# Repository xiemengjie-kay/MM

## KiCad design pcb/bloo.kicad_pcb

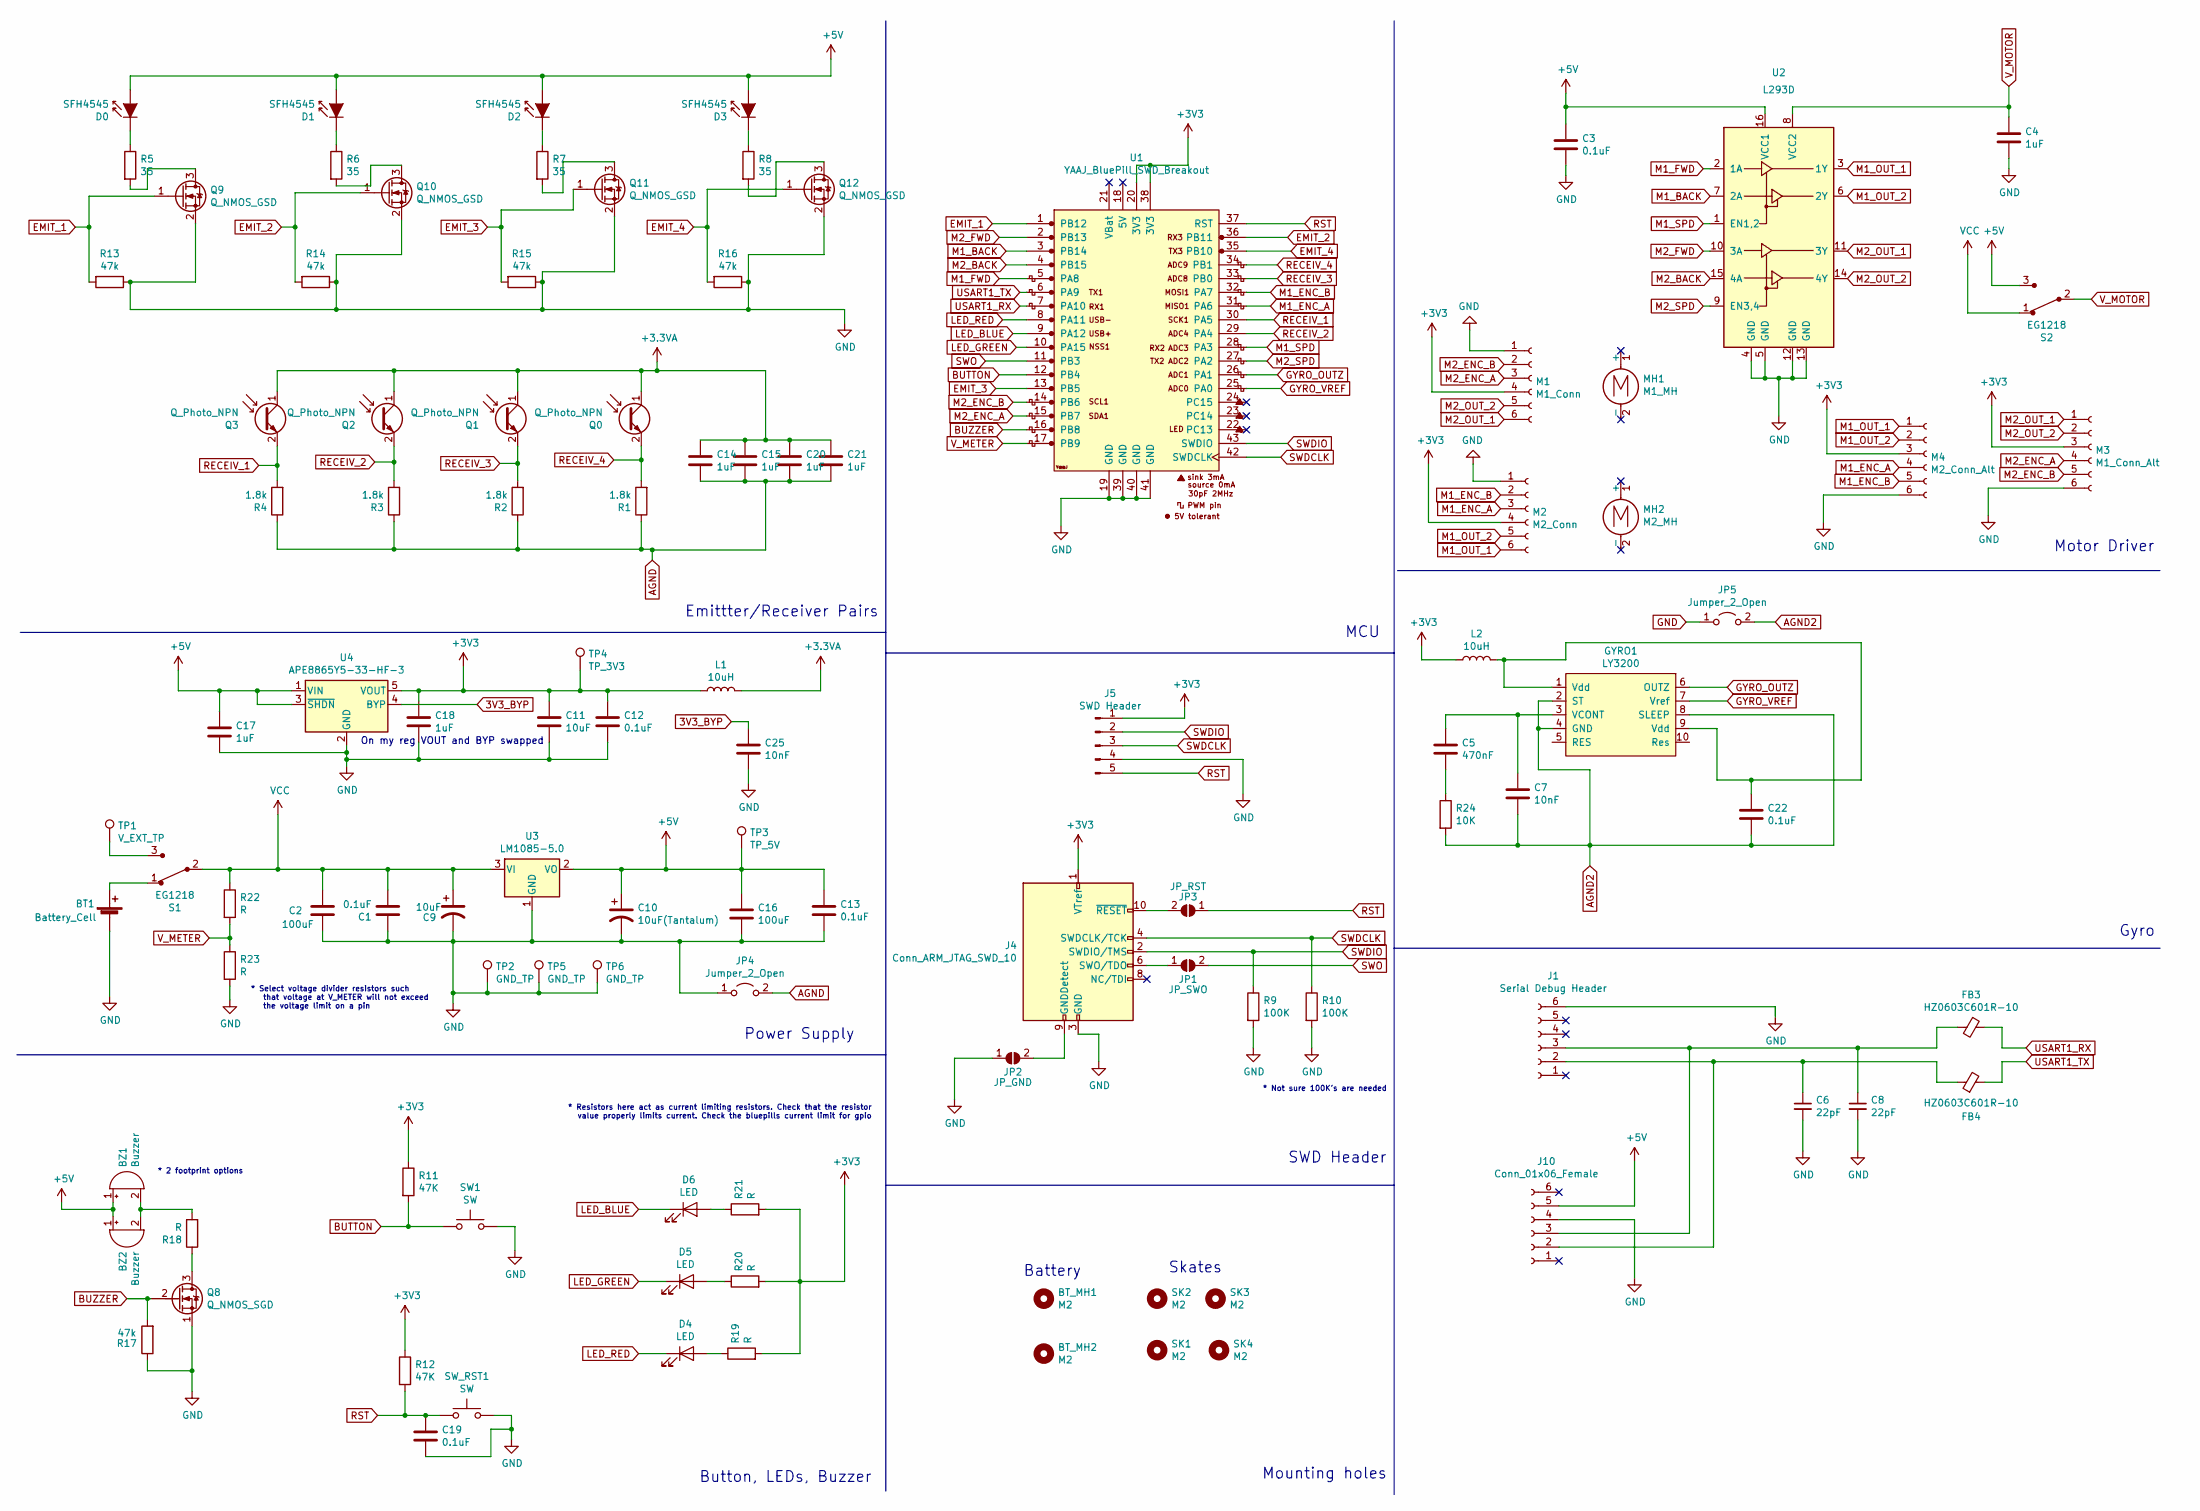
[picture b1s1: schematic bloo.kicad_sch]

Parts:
BT1: Battery_Cell; PinSocket_1x02_P2.54mm_Vertical
BT_MH1, BT_MH2: M2; MountingHole_2.2mm_M2
BZ1: Buzzer; Buzzer_12x9.5RM7.6
BZ2: Buzzer; Buzzer_TDK_PS1240P02BT_D12.2mm_H6.5mm
C1, C3, C12, C13, C19, C22: 0.1uF; C_1206_3216Metric_Pad1.33x1.80mm_HandSolder
C2, C16: 100uF; CP_Radial_D6.3mm_P2.50mm
C4, C14, C15, C17, C18, C20, C21: 1uF; C_1206_3216Metric_Pad1.33x1.80mm_HandSolder
C5: 470nF; C_1206_3216Metric_Pad1.33x1.80mm_HandSolder
C6, C8: 22pF; C_0603_1608Metric_Pad1.08x0.95mm_HandSolder
C7, C25: 10nF; C_1206_3216Metric_Pad1.33x1.80mm_HandSolder
C9, C11: 10uF; C_1206_3216Metric_Pad1.33x1.80mm_HandSolder
C10: 10uF(Tantalum); C_1206_3216Metric_Pad1.33x1.80mm_HandSolder
D0, D1, D2, D3: SFH4545; Emitter
D4, D5, D6: LED; LED_0805_2012Metric_Pad1.15x1.40mm_HandSolder
FB3, FB4: HZ0603C601R-10; R_0603_1608Metric_Pad0.98x0.95mm_HandSolder
GYRO1: LY3200; LGA10
J1: Serial Debug Header; PinHeader_1x06_P2.54mm_Vertical
J4: Conn_ARM_JTAG_SWD_10; PinHeader_2x05_P1.27mm_Vertical
J5: SWD Header; PinHeader_1x05_P2.54mm_Vertical
J10: Conn_01x06_Female; PinSocket_1x06_P2.54mm_Vertical
JP1: JP_SWO; SolderJumper-2_P1.3mm_Open_Pad1.0x1.5mm
JP2: JP_GND; SolderJumper-2_P1.3mm_Open_Pad1.0x1.5mm
JP3: JP_RST; SolderJumper-2_P1.3mm_Open_Pad1.0x1.5mm
JP4, JP5: Jumper_2_Open; SolderJumper-2_P1.3mm_Bridged_Pad1.0x1.5mm
L1, L2: 10uH; L_1206_3216Metric_Pad1.42x1.75mm_HandSolder
M1: M1_Conn; JST_SH_BM06B-SRSS-TB_1x06-1MP_P1.00mm_Vertical
M2: M2_Conn; JST_SH_BM06B-SRSS-TB_1x06-1MP_P1.00mm_Vertical
M3: M1_Conn_Alt; PinHeader_1x06_P2.54mm_Vertical
M4: M2_Conn_Alt; PinHeader_1x06_P2.54mm_Vertical
MH1: M1_MH; Motor_mouse
MH2: M2_MH; Motor_mouse
Q0, Q1, Q2, Q3: Q_Photo_NPN; Emitter
Q8: Q_NMOS_SGD; SOT-23
Q9, Q10, Q11, Q12: Q_NMOS_GSD; SOT-23
R1, R2, R3, R4: 1.8k; R_1206_3216Metric_Pad1.30x1.75mm_HandSolder
R5, R6, R7, R8: 35; R_1206_3216Metric_Pad1.30x1.75mm_HandSolder
R9, R10: 100K; R_1206_3216Metric_Pad1.30x1.75mm_HandSolder
R11, R12: 47K; R_1206_3216Metric_Pad1.30x1.75mm_HandSolder
R13, R14, R15, R16, R17: 47k; R_1206_3216Metric_Pad1.30x1.75mm_HandSolder
R18, R19, R20, R21, R22, R23: R; R_1206_3216Metric_Pad1.30x1.75mm_HandSolder
R24: 10K; R_1206_3216Metric_Pad1.30x1.75mm_HandSolder
S1, S2: EG1218; 1103M2S4CQE2; MPN EG1218; Digi-Key_PN EG1903-ND
SK1, SK2, SK3, SK4: M2; MountingHole_2.2mm_M2
SW1: SW; SW_SPST_REED_CT05-XXXX-G1
SW_RST1: SW; SW_SPST_REED_CT05-XXXX-G1
TP1: V_EXT_TP; PinHeader_1x01_P2.54mm_Vertical
TP2, TP5, TP6: GND_TP; PinHeader_1x01_P2.54mm_Vertical
TP3: TP_5V; PinHeader_1x01_P2.54mm_Vertical
TP4: TP_3V3; PinHeader_1x01_P2.54mm_Vertical
U1: YAAJ_BluePill_SWD_Breakout; YAAJ_BluePill_SWD_2
U2: L293D; DIP-16_W7.62mm
U3: LM1085-5.0; VREG_TO-263-3_TabPin2
U4: APE8865Y5-33-HF-3; SOT-23-5

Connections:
3V3_BYP: C25.1, U4.4 (BYP)
+3.3VA: C14.1, C15.1, C20.1, C21.1, L1.2, Q0.1 (C), Q1.1 (C), Q2.1 (C), Q3.1 (C)
+3V3: C11.1, C12.1, C18.1, J4.1 (VTref), J5.1, L1.1, L2.1, M1.4, M2.4, M3.3, M4.3, R11.1, R12.1, R19.2, R20.2, R21.2, TP4.1, U1.20 (3V3), U1.38 (3V3), U4.5 (VOUT); also elsewhere on the board
+5V: BZ1.1 (-), BZ2.1 (-), C3.1, C10.1, C13.1, C16.1, C17.1, D0.2 (A), D1.2 (A), D2.2 (A), D3.2 (A), J10.5, S2.3, TP3.1, U2.16 (VCC1), U3.2 (VO), U4.1 (VIN), U4.3 (~SHDN); also elsewhere on the board
AGND: C14.2, C15.2, C20.2, C21.2, JP4.2 (B), R1.1, R2.1, R3.1, R4.1
AGND2: C7.2, C22.2, GYRO1.2 (ST), GYRO1.4 (GND), GYRO1.8 (SLEEP), JP5.2 (B), R24.2
BUTTON: R11.2, SW1.1, U1.12 (PB4)
BUZZER: Q8.2 (G), R17.2, U1.16 (PB8)
EMIT_1: Q9.1 (G), R13.2, U1.1 (PB12)
EMIT_2: Q10.1 (G), R14.2, U1.36 (PB11)
EMIT_3: Q11.1 (G), R15.2, U1.13 (PB5)
EMIT_4: Q12.1 (G), R16.2, U1.35 (PB10)
GND: BT1.2 (-), C1.1, C2.2, C3.2, C4.2, C6.2, C8.2, C9.2, C10.2, C11.2, C12.2, C13.2, C16.2, C17.2, C18.2, C19.2, C25.2, J1.6, J4.3 (GND), J4.5 (GND), J5.4, J10.4, JP2.1 (A), JP4.1 (A), JP5.1 (A), M1.1, M2.1, M3.6, M4.6, Q8.1 (S), Q9.2 (S), Q10.2 (S), Q11.2 (S), Q12.2 (S), R9.2, R10.2, R13.1, R14.1, R15.1, R16.1, R17.1, R23.2, SW1.2, SW_RST1.2, TP2.1, TP5.1, TP6.1, U1.19 (GND), U1.39 (GND), U1.40 (GND), U1.41 (GND), U2.4 (GND), U2.5 (GND), U2.12 (GND), U2.13 (GND), U3.1 (GND), U4.2 (GND); also elsewhere on the board
GYRO_OUTZ: GYRO1.6 (OUTZ), U1.26 (PA1)
GYRO_VREF: GYRO1.7 (Vref), U1.25 (PA0)
LED_BLUE: D6.1 (K), U1.9 (PA12)
LED_GREEN: D5.1 (K), U1.10 (PA15)
LED_RED: D4.1 (K), U1.8 (PA11)
M1_BACK: U1.3 (PB14), U2.7 (2A)
M1_ENC_A: M2.3, M4.4, U1.31 (PA6)
M1_ENC_B: M2.2, M4.5, U1.32 (PA7)
M1_FWD: U1.5 (PA8), U2.2 (1A)
M1_OUT_1: M2.6, M4.1, U2.3 (1Y)
M1_OUT_2: M2.5, M4.2, U2.6 (2Y)
M1_SPD: U1.28 (PA3), U2.1 (EN1,2)
M2_BACK: U1.4 (PB15), U2.15 (4A)
M2_ENC_A: M1.3, M3.4, U1.15 (PB7)
M2_ENC_B: M1.2, M3.5, U1.14 (PB6)
M2_FWD: U1.2 (PB13), U2.10 (3A)
M2_OUT_1: M1.6, M3.1, U2.11 (3Y)
M2_OUT_2: M1.5, M3.2, U2.14 (4Y)
M2_SPD: U1.27 (PA2), U2.9 (EN3,4)
unnamed: BT1.1 (+), S1.1
unnamed: BZ1.2 (+), BZ2.2 (+), R18.2
unnamed: C5.1, C7.1, GYRO1.3 (VCONT)
unnamed: C5.2, R24.1
unnamed 36: C6.1, FB4.1, J1.2, J10.2; also elsewhere on the board
unnamed 37: C8.1, FB3.2, J1.3, J10.3; also elsewhere on the board
unnamed: C22.1, GYRO1.1 (Vdd), GYRO1.9 (Vdd), L2.2
unnamed: D0.1 (K), R5.1
unnamed: D1.1 (K), R6.1
unnamed: D2.1 (K), R7.1
unnamed: D3.1 (K), R8.1
unnamed: D4.2 (A), R19.1
unnamed: D5.2 (A), R20.1
unnamed: D6.2 (A), R21.1
unnamed: J4.6 (SWO/TDO), JP1.1 (A)
unnamed: J4.9 (GNDDetect), JP2.2 (B)
unnamed: J4.10 (~RESET), JP3.2 (B)
unnamed: Q8.3 (D), R18.1
unnamed: Q9.3 (D), R5.2
unnamed: Q10.3 (D), R6.2
unnamed: Q11.3 (D), R7.2
unnamed: Q12.3 (D), R8.2
unnamed: S1.3, TP1.1
RECEIV_1: Q3.2 (E), R4.2, U1.30 (PA5)
RECEIV_2: Q2.2 (E), R3.2, U1.29 (PA4)
RECEIV_3: Q1.2 (E), R2.2, U1.33 (PB0)
RECEIV_4: Q0.2 (E), R1.2, U1.34 (PB1)
RST: C19.1, J5.5, JP3.1 (A), R12.2, SW_RST1.1, U1.37 (RST); also elsewhere on the board
SWDCLK: J4.4 (SWDCLK/TCK), J5.3, R10.1, U1.42 (SWDCLK)
SWDIO: J4.2 (SWDIO/TMS), J5.2, R9.1, U1.43 (SWDIO)
SWO: JP1.2 (B), U1.11 (PB3)
USART1_RX: FB3.1, U1.7 (PA10)
USART1_TX: FB4.2, U1.6 (PA9)
VCC: C1.2, C2.1, C9.1, R22.1, S1.2, S2.1, U3.3 (VI)
V_METER: R22.2, R23.1, U1.17 (PB9)
V_MOTOR: C4.1, S2.2, U2.8 (VCC2)

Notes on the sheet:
SWD Header
* Resistors here act as current limiting resistors. Check that the resistor value properly limits current. Check the bluepills current limit for gpio
Emittter/Receiver Pairs
Motor Driver
Button, LEDs, Buzzer
MCU
Skates
Mounting holes
* Select voltage divider resistors such that voltage at V_METER will not exceed the voltage limit on a pin
Gyro
On my reg VOUT and BYP swapped
Battery
* 2 footprint options
Power Supply
* Not sure 100K’s are needed

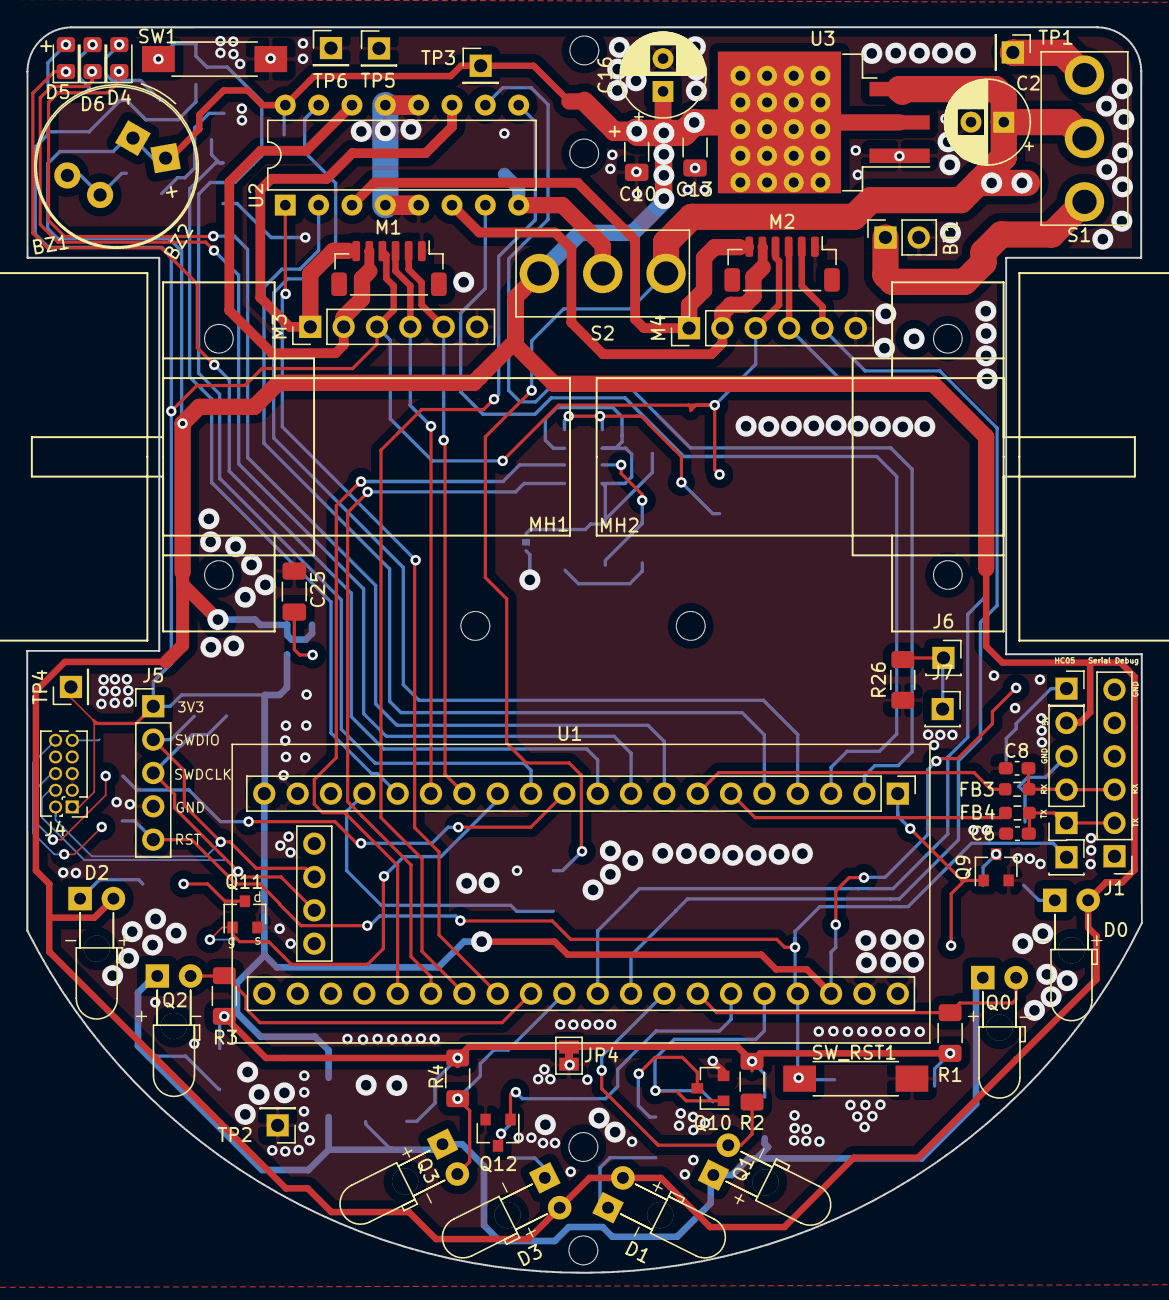
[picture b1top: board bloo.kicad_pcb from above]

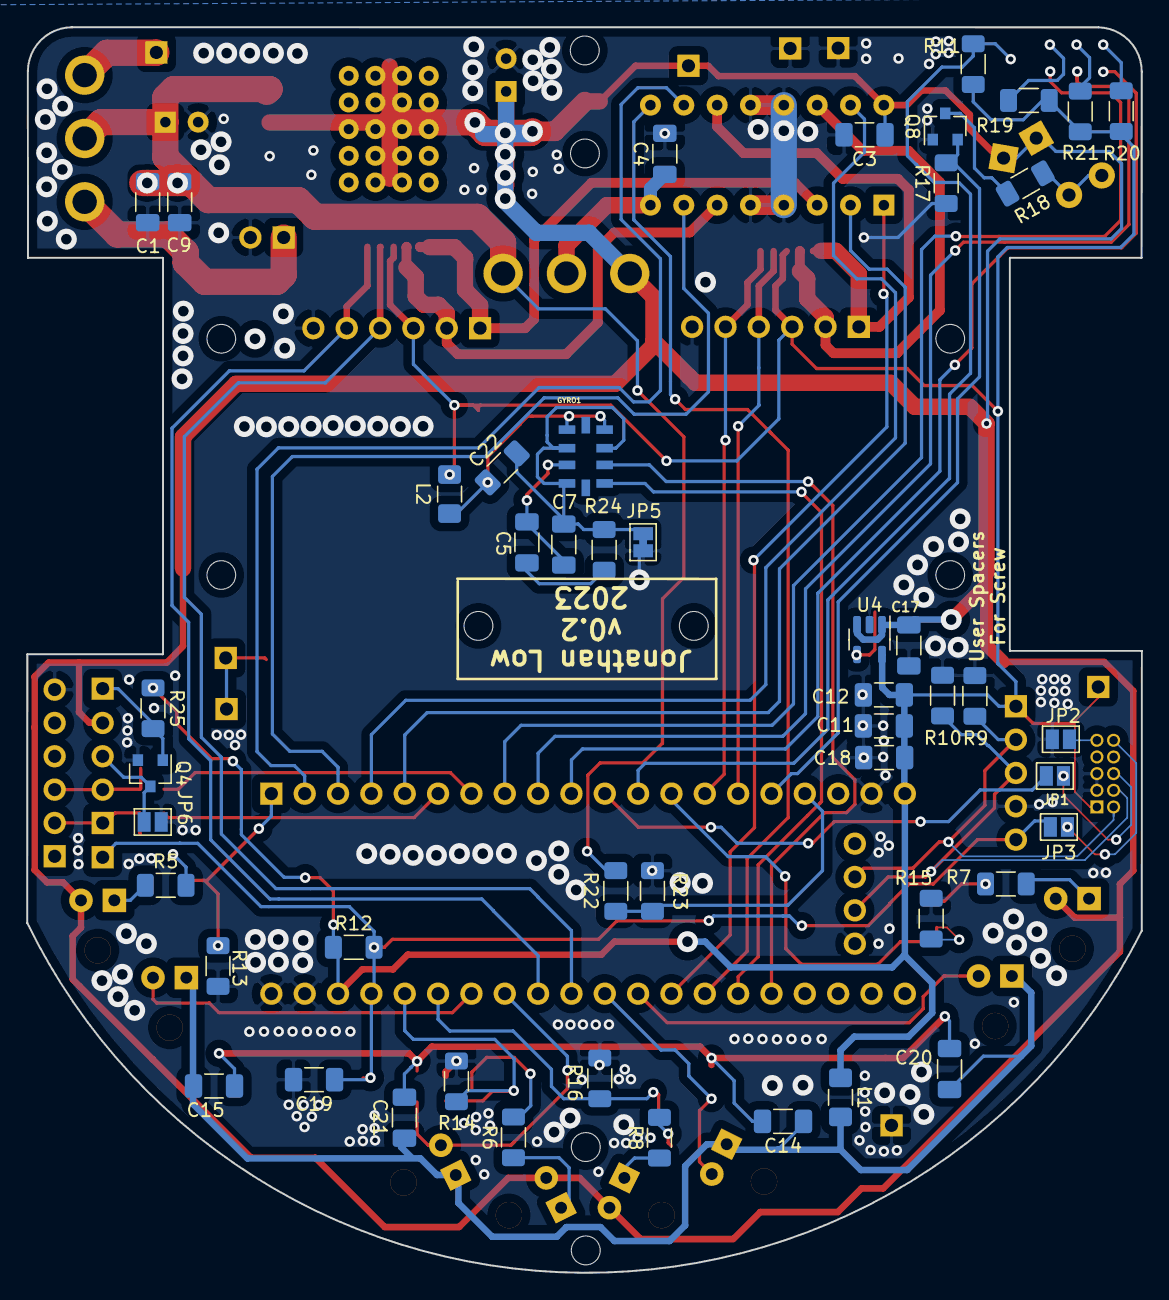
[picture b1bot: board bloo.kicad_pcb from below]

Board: 2 copper layers, 84.9 x 94.9 mm, 114 parts (48 on the bottom side), 71 nets.

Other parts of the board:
J2: Conn_RST; PinSocket_1x01_P2.54mm_Vertical
J3: BLE_PWR; PinSocket_1x01_P2.54mm_Vertical
J6, J7: BOOT0; PinSocket_1x01_P2.54mm_Vertical
J8: Conn_01x04_Female; PinSocket_1x04_P2.54mm_Vertical
JP6: Jumper_2_Open; SolderJumper-2_P1.3mm_Open_Pad1.0x1.5mm
Q4: Q_NMOS_GSD; SOT-23
R25, R26: 47k; R_1206_3216Metric_Pad1.30x1.75mm_HandSolder

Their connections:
+3V3: R25.1; also elsewhere on the board
+5V: J8.4; also elsewhere on the board
GND: JP6.2, Q4.2, R26.1; also elsewhere on the board
unnamed 36: J8.1; also elsewhere on the board
unnamed 37: J8.2; also elsewhere on the board
unnamed: J3.1, Q4.1, R25.2
unnamed: J6.1, J7.1, R26.2
unnamed: J8.3, JP6.1, Q4.3
RST: J2.1; also elsewhere on the board

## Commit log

2023-08-31 pcb design
